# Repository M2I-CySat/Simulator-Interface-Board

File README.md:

These are the KiCad project files for the Fall 2025 CySat Simulator interface board for HASP.
KiCAD files in this branch will include part for thermal camera integration

The files to submit to JLCPCB are in jlcpcb/production_files; the DigiKey BOM is in the main directory.

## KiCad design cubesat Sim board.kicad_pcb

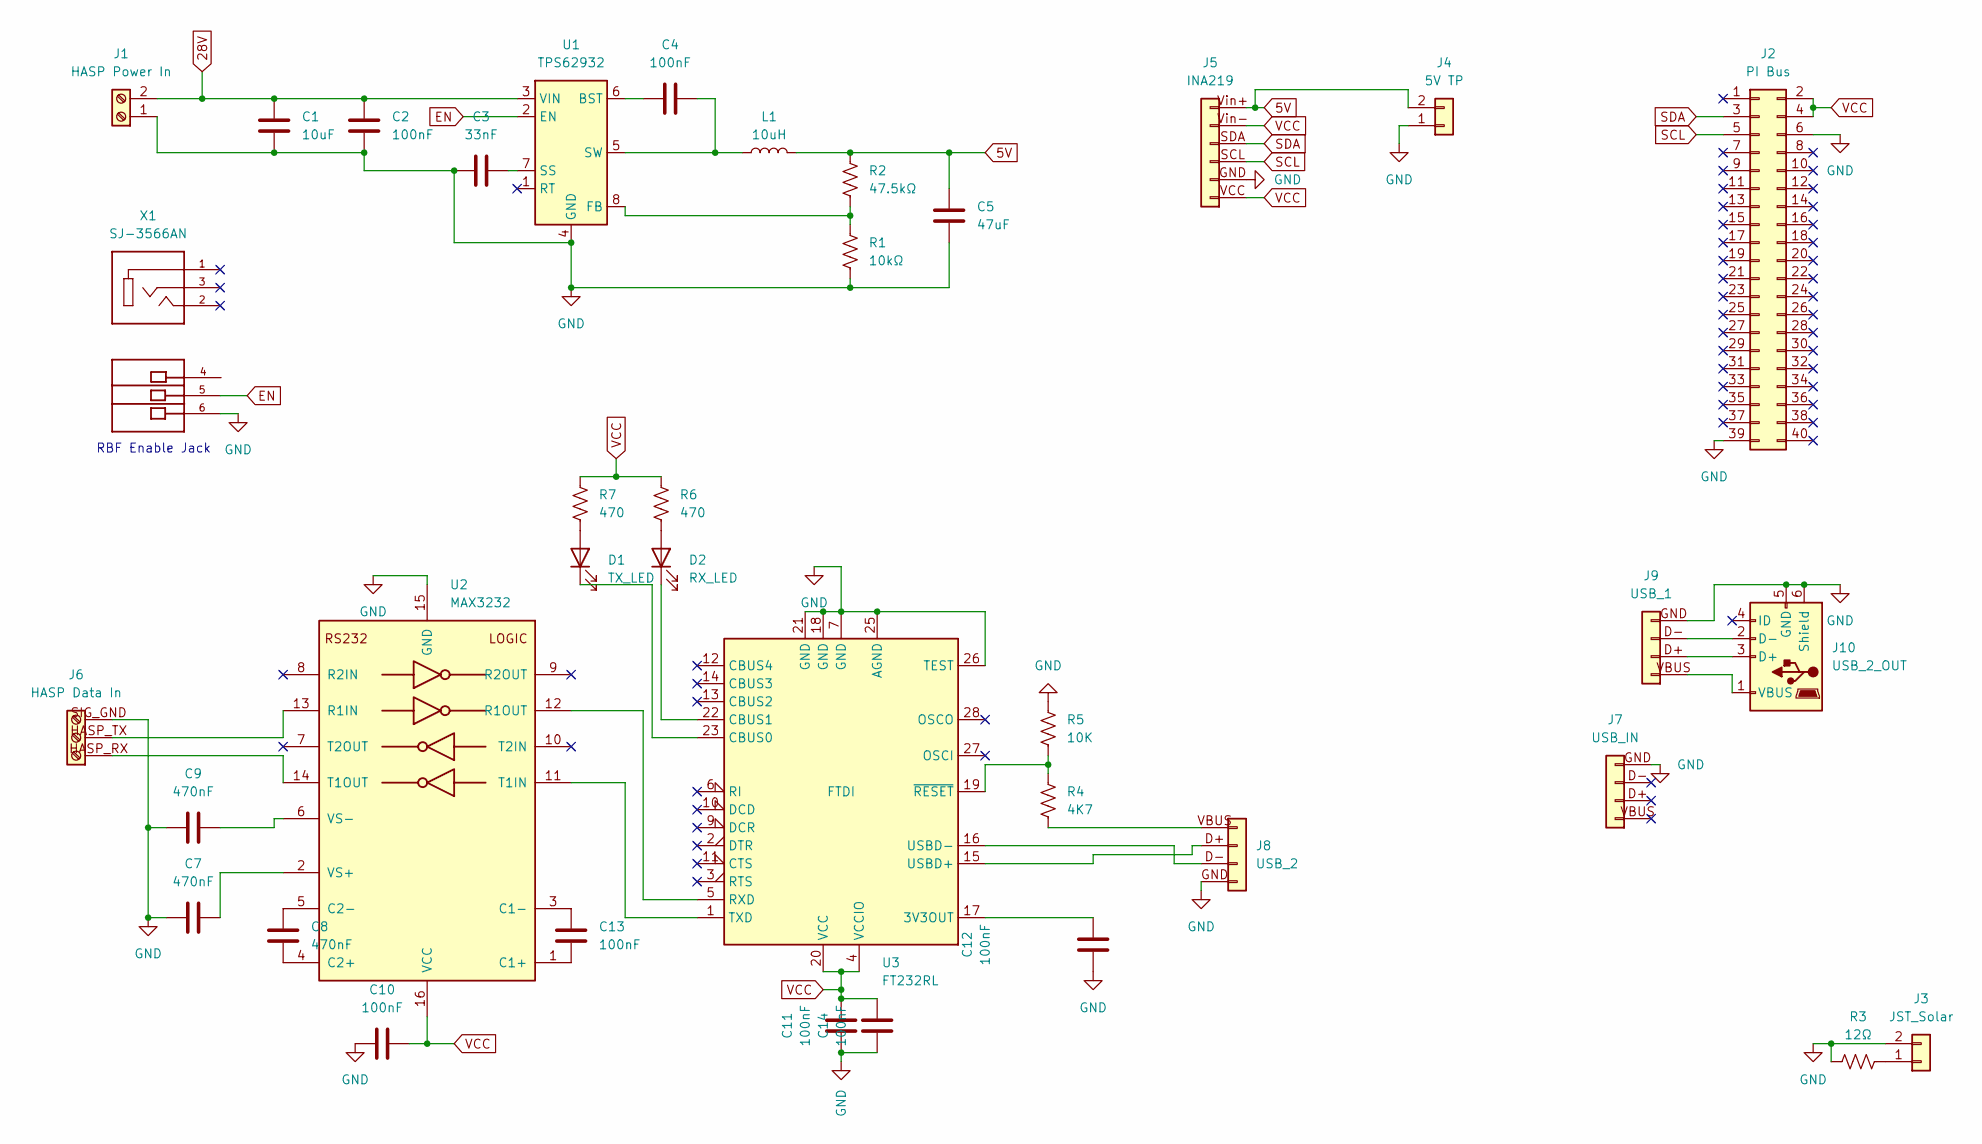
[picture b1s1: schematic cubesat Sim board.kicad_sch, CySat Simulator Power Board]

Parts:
C1: 10uF; C_0805_2012Metric
C2, C4, C10, C11, C12, C13, C14: 100nF; C_0603_1608Metric
C3: 33nF; C_0603_1608Metric
C5: 47uF; C_1206_3216Metric
C7, C8, C9: 470nF; C_0603_1608Metric
D1: TX_LED; LED_0603_1608Metric
D2: RX_LED; LED_0603_1608Metric
J1: HASP Power In; CONN_OSTVN02A150_OST
J2: PI Bus; PinSocket_2x20_P2.54mm_Vertical
J3: JST_Solar; JST_PH_B2B-PH-K_1x02_P2.00mm_Vertical
J4: 5V TP; JST_PH_B2B-PH-K_1x02_P2.00mm_Vertical
J5: INA219; PinHeader_1x06_P2.54mm_Vertical
J6: HASP Data In; CONN3_OSTVN03A150_OST
J7: USB_IN; PinHeader_1x04_P2.54mm_Vertical_USB
J8: USB_2; PinHeader_1x04_P2.54mm_Vertical_USB
J9: USB_1; PinHeader_1x04_P2.54mm_Vertical_USB
J10: USB_2_OUT; USB_Micro-B_Amphenol_10118194-0001LF_Horizontal
L1: 10uH; L_Bourns_SRR1208_12.7x12.7mm
R1: 10kΩ; R_Axial_DIN0207_L6.3mm_D2.5mm_P2.54mm_Vertical
R2: 47.5kΩ; R_Axial_DIN0207_L6.3mm_D2.5mm_P2.54mm_Vertical
R3: 12Ω; R_Axial_DIN0614_L14.3mm_D5.7mm_P15.24mm_Horizontal
R4: 4K7; R_0603_1608Metric
R5: 10K; R_0603_1608Metric
R6, R7: 470; R_0603_1608Metric
U1: TPS62932; SOT-583-8
U2: MAX3232; SOIC-16_3.9x9.9mm_P1.27mm
U3: FT232RL; SSOP-28_5.3x10.2mm_P0.65mm
X1: SJ-3566AN; CUI_SJ-3566AN

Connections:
5V: C5.2, J4.2, J5.Vin+ (Pin_6), L1.2, R2.1
28V: C1.1, C2.1, J1.2, U1.3 (VIN)
EN: U1.2 (EN), X1.5
GND: C1.2, C2.2, C3.1, C5.1, C7.1, C9.2, C10.1, C11.1, C12.1, C14.1, J1.1, J2.6, J2.39, J3.2, J4.1, J5.GND (Pin_2), J6.SIG_GND (Pin_3), J7.GND (Pin_4), J8.GND (Pin_4), J9.GND (Pin_4), J10.5 (GND), J10.6 (Shield), R1.2, R3.1, R5.1, U1.4 (GND), U2.15 (GND), U3.7 (GND), U3.18 (GND), U3.21 (GND), U3.25 (AGND), U3.26 (TEST), X1.6
unnamed: D1.2 (A), R7.2
unnamed: D1.1 (K), U3.23 (CBUS0)
unnamed: D2.2 (A), R6.2
unnamed: D2.1 (K), U3.22 (CBUS1)
unnamed: J3.1, R3.2
unnamed: J6.HASP_RX (Pin_1), U2.14 (T1OUT)
unnamed: J6.HASP_TX (Pin_2), U2.13 (R1IN)
unnamed: J8.VBUS (Pin_1), R4.2
unnamed: J8.D+ (Pin_2), U3.15 (USBD+)
unnamed: J8.D- (Pin_3), U3.16 (USBD-)
unnamed: J9.D+ (Pin_2), J10.3 (D+)
unnamed: J9.D- (Pin_3), J10.2 (D-)
unnamed: J9.VBUS (Pin_1), J10.1 (VBUS)
unnamed: C4.1, U1.6 (BST)
unnamed: R1.1, R2.2, U1.8 (FB)
unnamed: C3.2, U1.7 (SS)
unnamed: C4.2, L1.1, U1.5 (SW)
unnamed: C13.1, U2.1 (C1+)
unnamed: C13.2, U2.3 (C1-)
unnamed: C8.1, U2.4 (C2+)
unnamed: C8.2, U2.5 (C2-)
unnamed: U2.12 (R1OUT), U3.5 (RXD)
unnamed: U2.11 (T1IN), U3.1 (TXD)
unnamed: C7.2, U2.2 (VS+)
unnamed: C9.1, U2.6 (VS-)
unnamed: C12.2, U3.17 (3V3OUT)
unnamed: R4.1, R5.2, U3.19 (~RESET)
SCL: J2.5, J5.SCL (Pin_3)
SDA: J2.3, J5.SDA (Pin_4)
VCC: C10.2, C11.2, C14.2, J2.2, J2.4, J5.VCC (Pin_1), J5.Vin- (Pin_5), R6.1, R7.1, U2.16 (VCC), U3.4 (VCCIO), U3.20 (VCC)

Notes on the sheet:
RBF Enable Jack

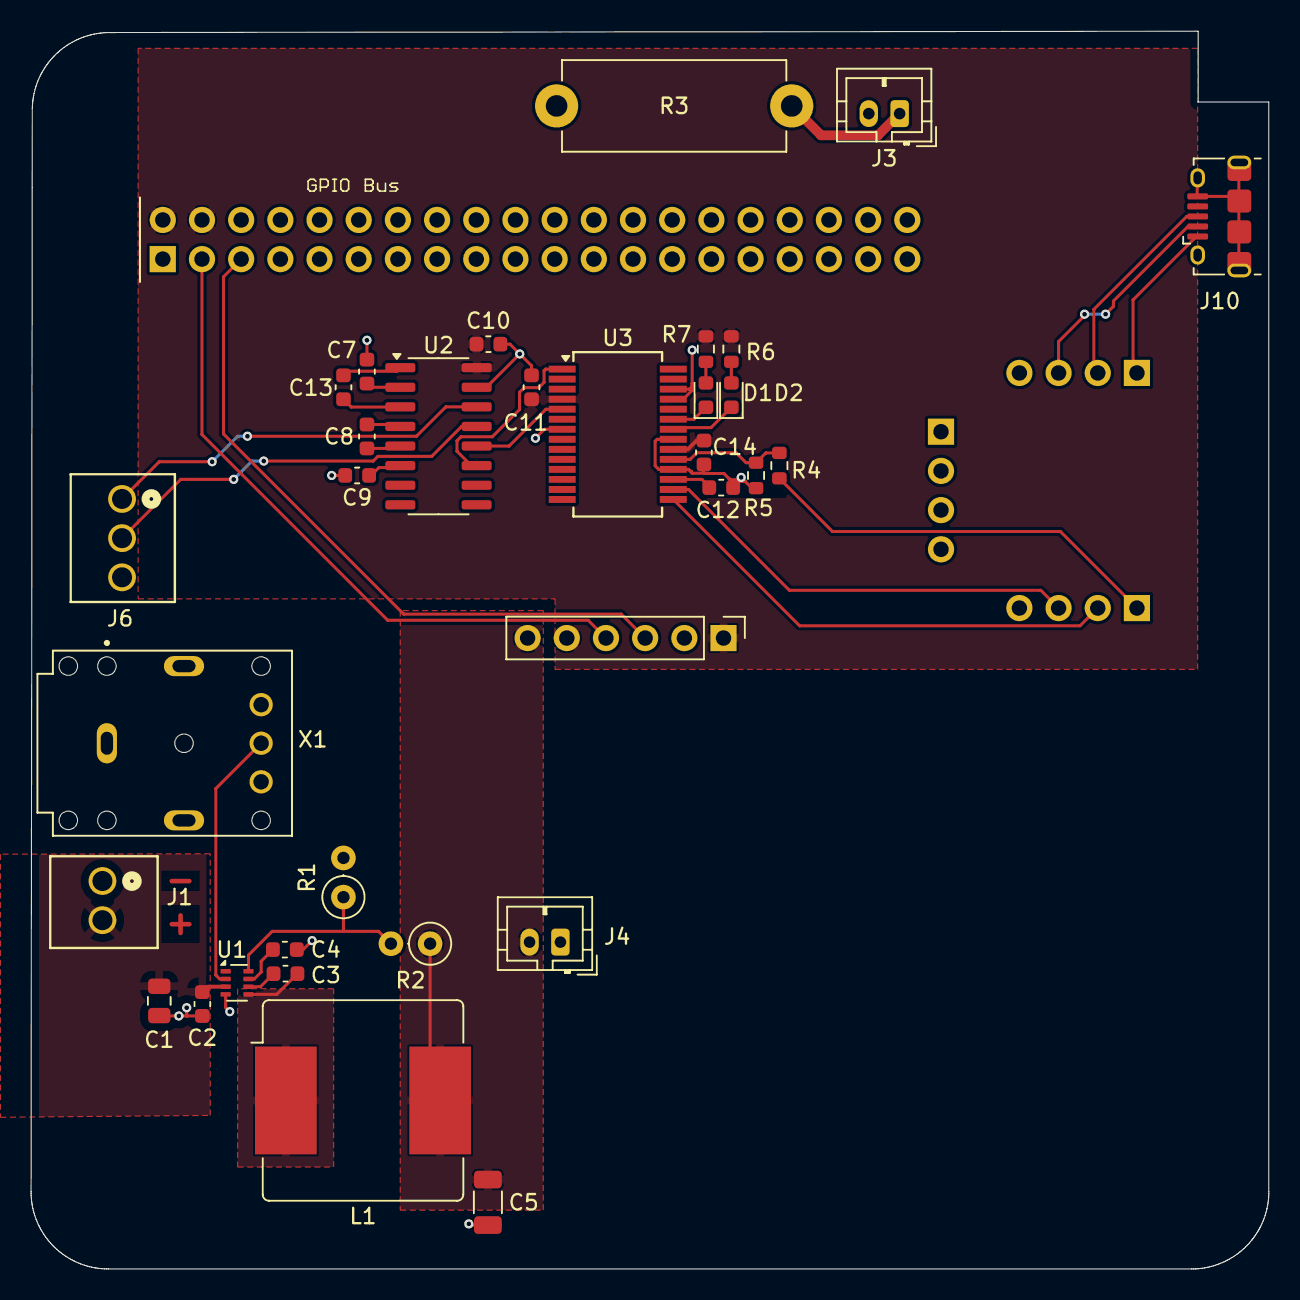
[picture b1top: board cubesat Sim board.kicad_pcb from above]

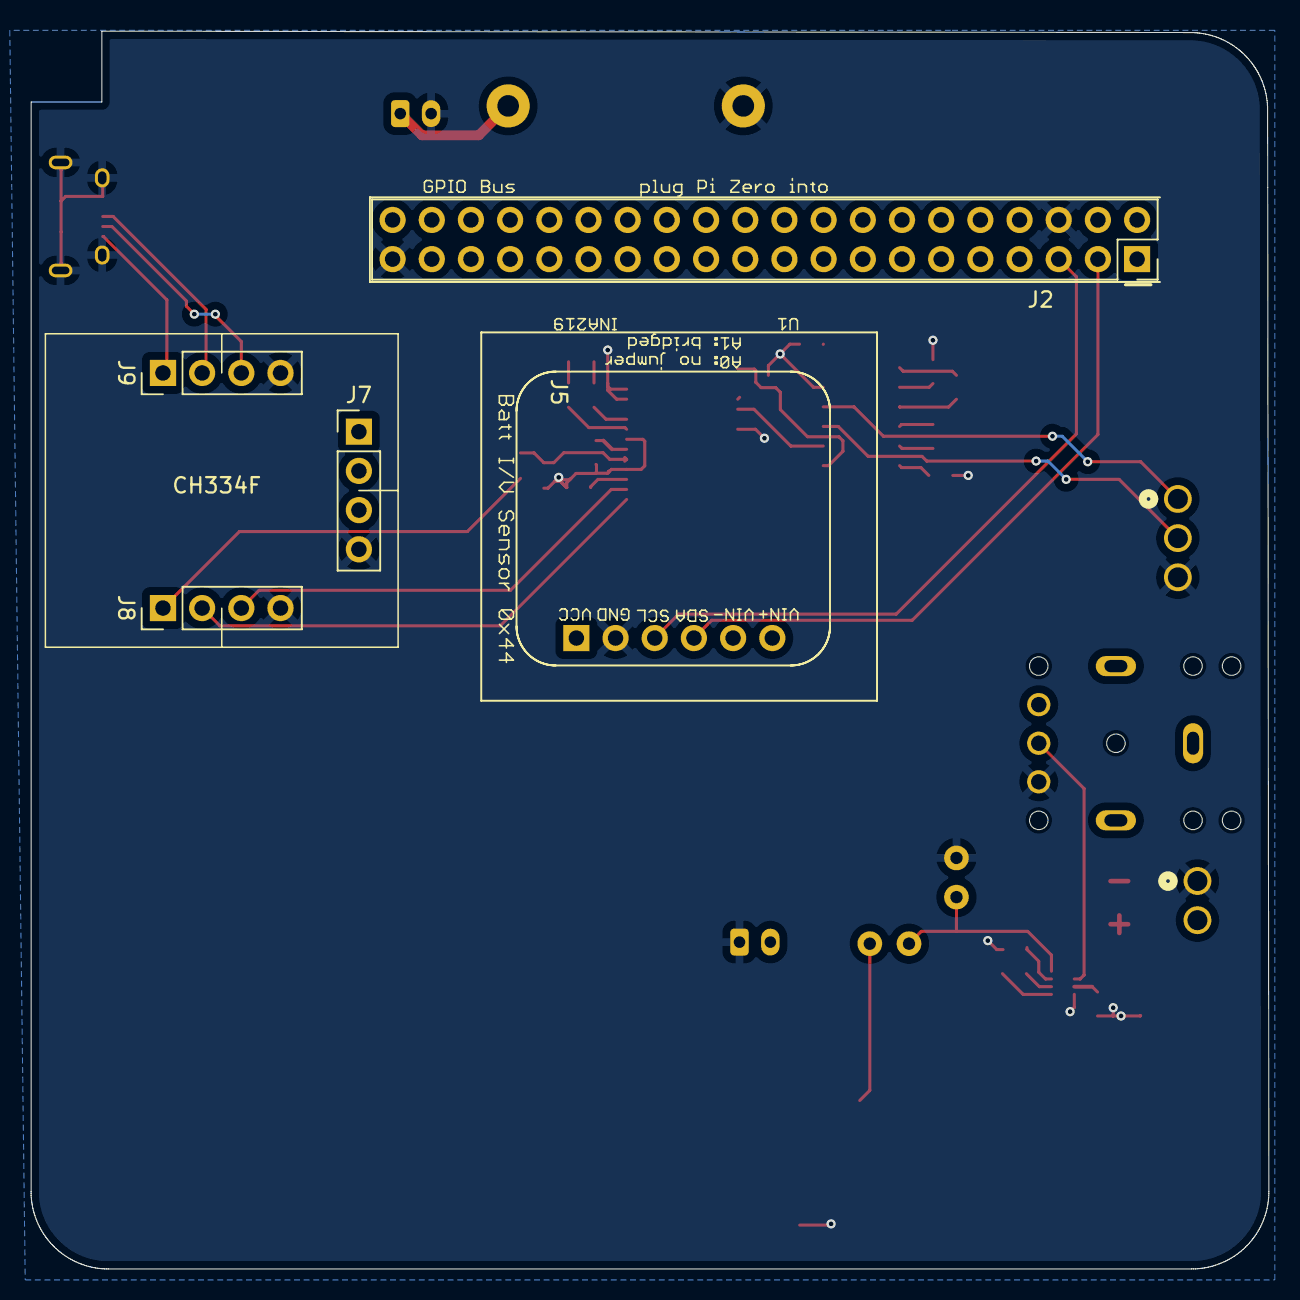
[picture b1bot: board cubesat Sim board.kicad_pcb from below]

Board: 2 copper layers, 80.2 x 80.2 mm, 37 parts (4 on the bottom side), 34 nets.

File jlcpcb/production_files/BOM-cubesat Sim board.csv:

Comment,Designator,Footprint,LCSC,Quantity
100nF,"C10,C11,C12,C13,C14,C2,C4",C_0603_1608Metric,C14663,7
10K,R5,R_0603_1608Metric,C25804,1
10uF,C1,C_0805_2012Metric,C440198,1
10uH,L1,L_Bourns_SRR1208_12.7x12.7mm,C2041331,1
33nF,C3,C_0603_1608Metric,C21117,1
470,"R6,R7",R_0603_1608Metric,C23179,2
470nF,"C7,C8,C9",C_0603_1608Metric,C1623,3
4K7,R4,R_0603_1608Metric,C23162,1
FT232RL,U3,SSOP-28_5.3x10.2mm_P0.65mm,C8690,1
MAX3232,U2,SOIC-16_3.9x9.9mm_P1.27mm,C193666,1
RX_LED,D2,LED_0603_1608Metric,C2290,1
TPS62932,U1,SOT-583-8,C3032935,1
TX_LED,D1,LED_0603_1608Metric,C2286,1
USB_2_OUT,J10,USB_Micro-B_Amphenol_10118194-0001LF_Horizontal,C132563,1
47uF,C5,C_1206_3216Metric,,1

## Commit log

2025-11-07 Add files via upload
    Initial Commit
2025-11-07 BOM
    Updated BOMs
2025-11-07 Add project description to README.md
2025-11-10 Added cutout for mounting
    Added cutout for mounting as requested by structures team
2026-02-19 Added datasheet for regulator
2026-03-03 Fixes to some ERC checks. Tracking down a potential short issue.
